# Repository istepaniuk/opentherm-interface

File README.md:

# opentherm-interface
Firmware for the OpenTherm/plus standalone interface

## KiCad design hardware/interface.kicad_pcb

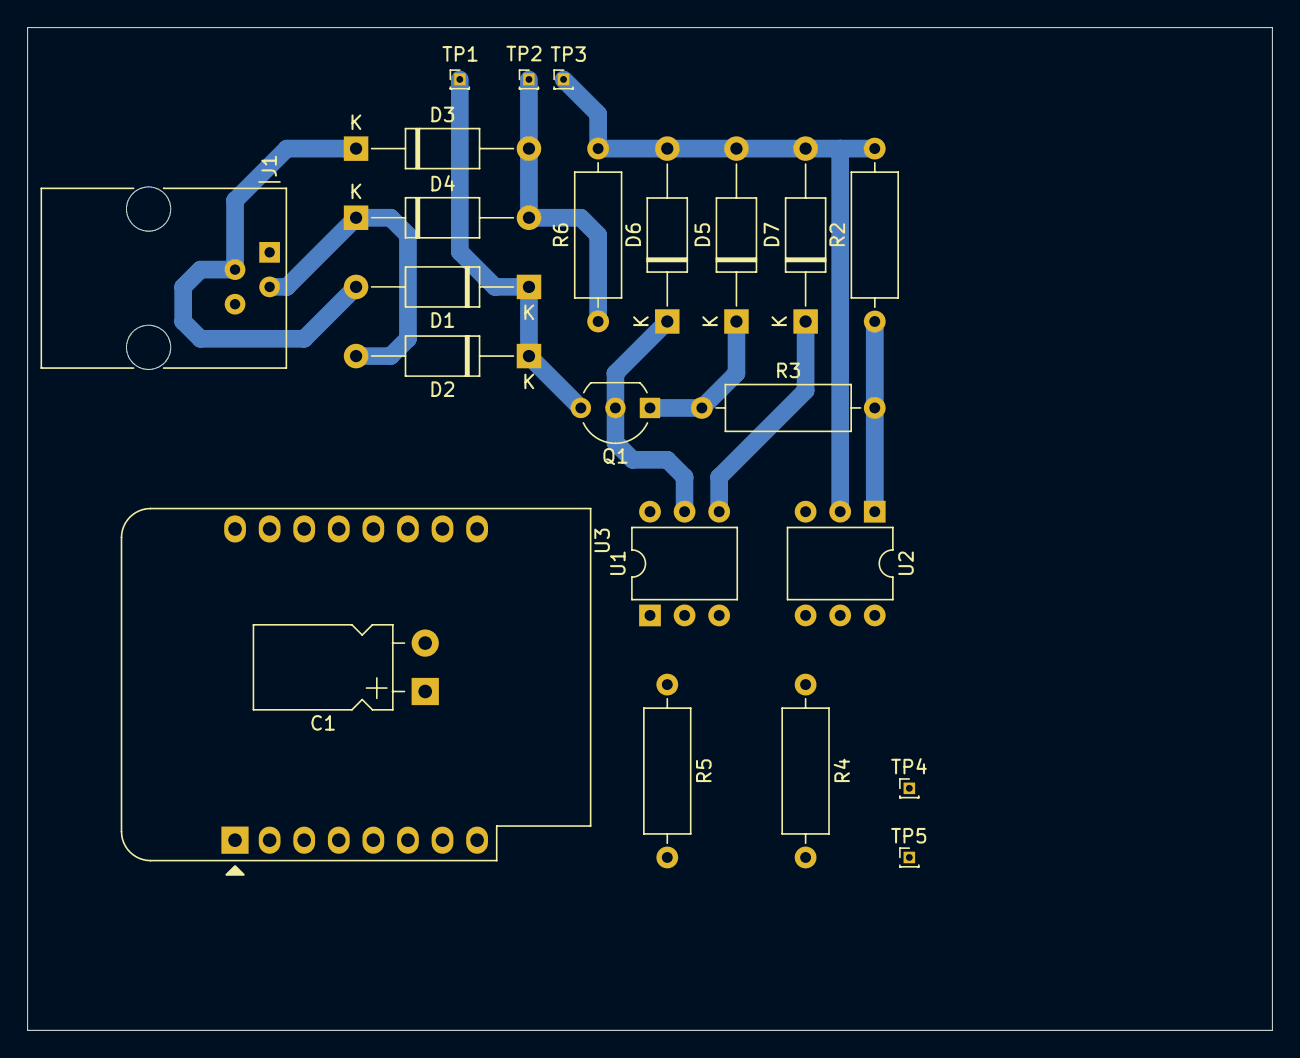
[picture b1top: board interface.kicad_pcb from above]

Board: 2 copper layers, 91.4 x 73.7 mm, 23 parts (0 on the bottom side), 14 nets.

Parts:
C1: 3.3uF; CP_Radial_L10.0mm_D6.0mm_Sideways
D1, D2, D3, D4: 1N4148; D_A-405_P12.70mm_Horizontal
D5: 4.7V; D_A-405_P12.70mm_Horizontal
D6: 15V; D_A-405_P12.70mm_Horizontal
D7: 4.3V; D_A-405_P12.70mm_Horizontal
J1: RJ11; RJ11_4
Q1: BC558; TO-92_Inline_Wide
R2: 100; R_Axial_DIN0309_L9.0mm_D3.2mm_P12.70mm_Horizontal
R3: 220; R_Axial_DIN0309_L9.0mm_D3.2mm_P12.70mm_Horizontal
R4: 330; R_Axial_DIN0309_L9.0mm_D3.2mm_P12.70mm_Horizontal
R5: 1K5; R_Axial_DIN0309_L9.0mm_D3.2mm_P12.70mm_Horizontal
R6: 1; R_Axial_DIN0309_L9.0mm_D3.2mm_P12.70mm_Horizontal
TP1: OT+; PinHeader_1x01_P1.00mm_Vertical
TP2: OT-; PinHeader_1x01_P1.00mm_Vertical
TP3: CS; PinHeader_1x01_P1.00mm_Vertical
TP4: OUT; PinHeader_1x01_P1.00mm_Vertical
TP5: IN; PinHeader_1x01_P1.00mm_Vertical
U1, U2: 4N28; DIP-6_W7.62mm
U3: WeMos D1m; WEMOS_D1_mini_light

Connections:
+3V3: C1.1, U2.5, U3.8
/X1: D2.2, D4.1, J1.3
/X2: D1.2, D3.1, J1.2
GND: C1.2, R5.1, U1.2, U3.10
unnamed: D1.1, D2.1, Q1.3, TP1.1
unnamed: D3.2, D4.2, R6.1, TP2.1
unnamed: D5.1, Q1.1, R3.1
unnamed: D5.2, D6.2, D7.2, R2.2, R6.2, TP3.1, U2.2
unnamed: D6.1, Q1.2, U1.5
unnamed: D7.1, U1.4
unnamed: R2.1, R3.2, U2.1
unnamed: R4.1, U1.1
unnamed: R4.2, TP4.1, U3.14
unnamed: R5.2, TP5.1, U2.4, U3.6

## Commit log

2020-04-16 initial commit, including Jiří Praus library
2020-04-16 work-in-progress KiCad files
2020-04-16 Create LICENSE
    Matching the library license
2020-04-16 copyright notice
2020-04-20 less chatty, debug levels, removed modulation support
